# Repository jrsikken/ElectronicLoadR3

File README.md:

# Jasper's Electronic Load R3
This repositiry contains the open source hardware files. This device is an Arduino compatible Electronic Load. It is intended for testing DC power supplies, solar panels and batteries. It supports pulsed loads!
I am selling on Tindie https://www.tindie.com/products/jaspersikken/jaspers-electronic-load-r3/
Technical details are also found there.

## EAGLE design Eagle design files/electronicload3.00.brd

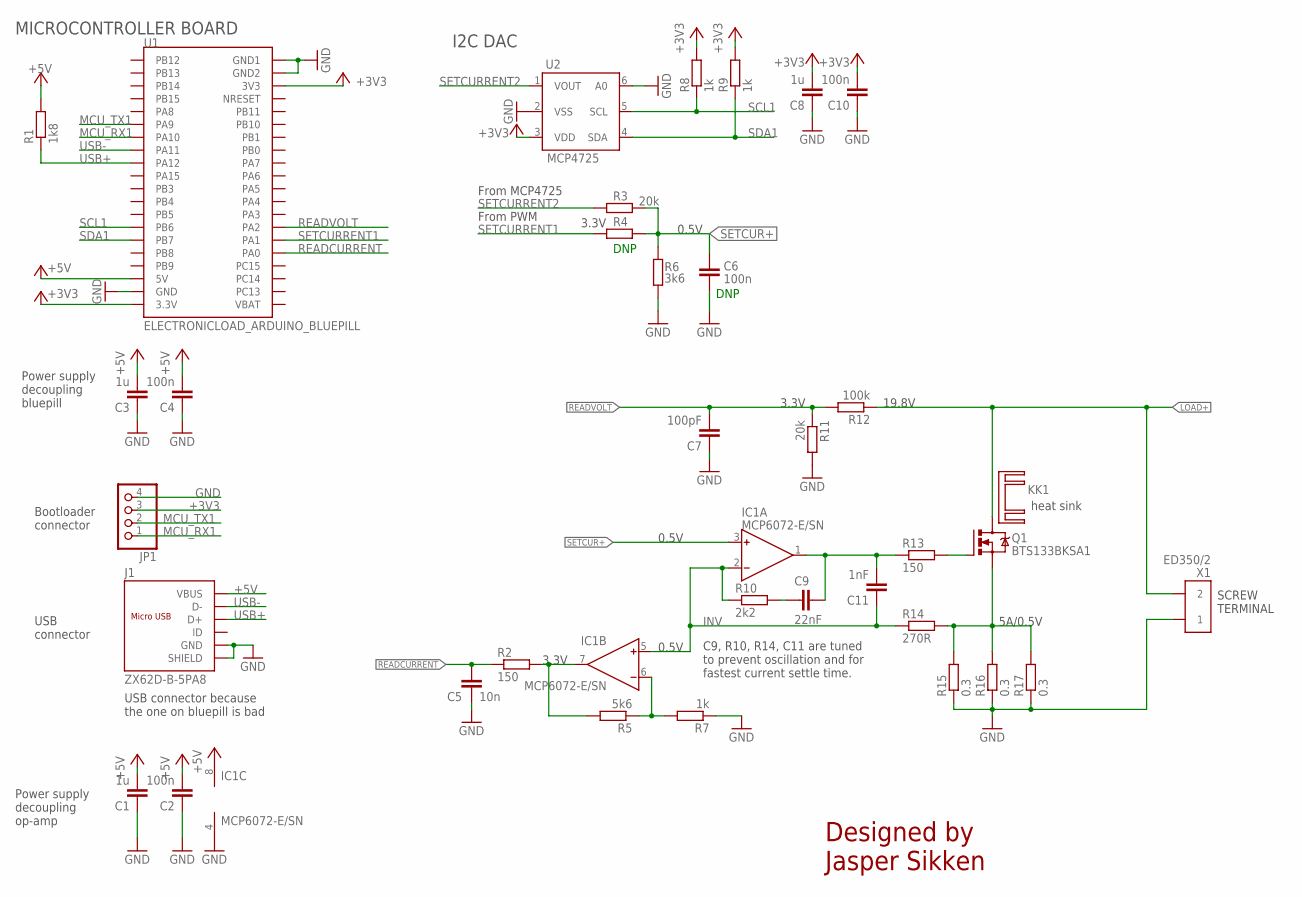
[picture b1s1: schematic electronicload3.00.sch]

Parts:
C1, C3, C8: 1u; C0603K; TOLERANCE 10%; VOLTAGE 16V; DIGIKEY 311-1444-1-ND
C2, C4, C10: 100n; C0603K; TOLERANCE 10%; VOLTAGE 50V; DIGIKEY 445-7456-1-ND
C5: 10n; C0603K; TOLERANCE 10%; VOLTAGE 50V; DIGIKEY 445-7456-1-ND
C6: 100n; C0603K; TOLERANCE 10%; VOLTAGE 50V; DIGIKEY 445-12511-1-ND
C7: 100pF; C0603K; TOLERANCE 10%; VOLTAGE 50V; DIGIKEY 445-7456-1-ND
C9: 22nF; C0603K; TOLERANCE 10%; VOLTAGE 50V; DIGIKEY 445-7456-1-ND
C11: 1nF; C0603K; TOLERANCE 10%; VOLTAGE 50V; DIGIKEY 445-7456-1-ND
IC1: MCP6072-E/SN; SO8
J1: ZX62D-B-5PA8; MICRO-USB5+6P-SMD-0.65-AB
JP1: PINHD-1X4; 1X04
KK1: SK129; SK129-HOLE
Q1: BTS133BKSA1; TO220BV; DIGIKEY BTS133BKSA1-ND
R1: 1k8; R0603; DIGIKEY RMCF0603JT18K0CT-ND
R2, R13: 150; R0603; DIGIKEY RMCF0603JT150RCT-ND
R3, R4: 20k; R0603; DIGIKEY RMCF0603JT18K0CT-ND
R5: 5k6; R0603; DIGIKEY RMCF0603JT180KCT-ND
R6: 3k6; R0603; DIGIKEY RMCF0603JT18K0CT-ND
R7: 1k; R0603; DIGIKEY RMCF0603JT20K0CT-ND
R8, R9: 1k; R0603; DIGIKEY RMCF0603JT10K0CT-ND
R10: 2k2; R0603; DIGIKEY RMCF0603JT150RCT-ND
R11: 20k; R0603; DIGIKEY RMCF0603JT20K0CT-ND
R12: 100k; R0603; DIGIKEY RMCF0603JT100KCT-ND
R14: 270R; R0603; DIGIKEY RMCF0603JT150RCT-ND
R15, R16, R17: 0.3; R2512
U1: ELECTRONICLOAD_ARDUINO_BLUEPILL
U2: MCP4725; SOT-23-6
X1: ED350/2

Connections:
+3V3: C8.2, C10.2, JP1.3, R8.2, R9.2, U1.P$17 (3V3), U1.P$39 (3.3V), U2.3 (VDD)
+5V: C1.2, C2.2, C3.2, C4.2, IC1.8 (V+), J1.1 (VBUS), R1.2, U1.P$37 (5V)
AOUT: C9.1, C11.2, IC1.1 (OUT), R13.1
GATE: Q1.G, R13.2
GND: C1.1, C2.1, C3.1, C4.1, C5.1, C6.1, C7.1, C8.1, C10.1, IC1.4 (V-), J1.5 (GND), J1.P1 (SHIELD), J1.P2 (SHIELD), J1.P3 (SHIELD), J1.P4 (SHIELD), J1.P5 (SHIELD), J1.P6 (SHIELD), JP1.4, R6.1, R7.1, R11.2, R15.1, R16.1, R17.1, U1.P$18 (GND2), U1.P$19 (GND1), U1.P$38 (GND), U2.2 (VSS), U2.6 (A0), X1.P$1 (1)
INV: C11.1, IC1.2 (IN-), IC1.5 (IN+), R10.1, R14.1
LOAD+: Q1.D, R12.1, X1.P$2 (2)
MCU_RX1: JP1.1, U1.P$26 (PA10)
MCU_TX1: JP1.2, U1.P$25 (PA9)
unnamed: Q1.S, R14.2, R15.2, R16.2, R17.2
unnamed: IC1.6 (IN-), R5.1, R7.2
unnamed: C9.2, R10.2
unnamed: IC1.7 (OUT), R2.2, R5.2
READCURRENT: C5.2, R2.1, U1.P$4 (PA0)
READVOLT: C7.2, R11.1, R12.2, U1.P$6 (PA2)
SCL1: R8.1, U1.P$33 (PB6), U2.5 (SCL)
SDA1: R9.1, U1.P$34 (PB7), U2.4 (SDA)
SETCUR+: C6.2, IC1.3 (IN+), R3.1, R4.1, R6.2
SETCURRENT1: R4.2, U1.P$5 (PA1)
SETCURRENT2: R3.2, U2.1 (VOUT)
USB+: J1.3 (D+), R1.1, U1.P$28 (PA12)
USB-: J1.2 (D-), U1.P$27 (PA11)

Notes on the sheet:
SCREW TERMINAL
19.8V
3.3V
MICROCONTROLLER BOARD
I2C DAC
Bootloader connector
From MCP4725
From PWM
DNP
Designed by Jasper Sikken
USB connector because the one on bluepill is bad
USB connector
Power supply decoupling bluepill
Power supply decoupling op-amp
heat sink
C9, R10, R14, C11 are tuned to prevent oscillation and for fastest current settle time.
5A/0.5V
0.5V

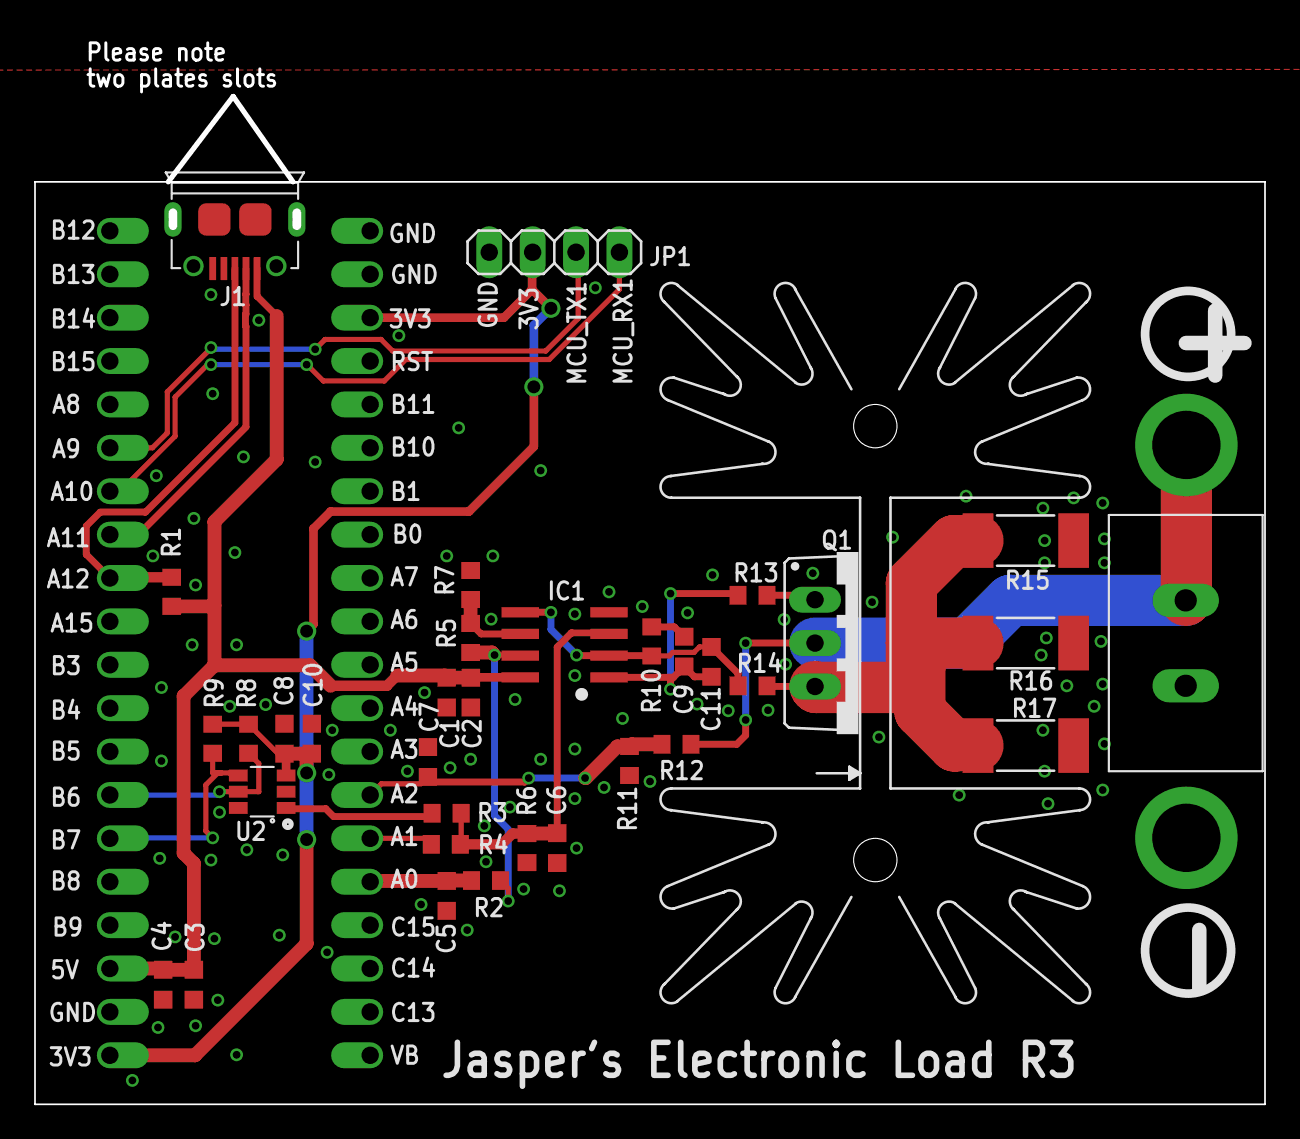
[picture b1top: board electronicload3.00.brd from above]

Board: 2 copper layers, 72.0 x 59.0 mm, 36 parts (0 on the bottom side), 22 nets.

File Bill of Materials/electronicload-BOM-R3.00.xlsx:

Qty | Value | Device | Package | Parts | Description | DIGIKEY | FARNELL_OC | MF | MOUSER_OC | MPN | SPICEPREFIX | TEMPCOEFF | TOLERANCE | VALUE.1 | VOLTAGE | Column1
3 | 0.3 | R2512_10R | R2512 | R15, R16, R17 | Resistor |  | 2426553
1 | 100k | R-EU_R0603 | R0603 | R12 | Resistor |  |  |  |  |  | R
3 | 100n | C-EUC0603K | C0603K | C2, C4, C10 | Capacitor |  |  |  |  |  | C | X5R | 0.1 |  | 50V
1 | 1nF | C-EUC0603K | C0603K | C11 | Capacitor
1 | 10nF | C-EUC0603K | C0603K | C5 | Capacitor
1 | 22nF | C-EUC0603K | C0603K | C9 | Capacitor
1 | 100pF | C-EUC0603K | C0603K | C7 | Capacitor
2 | 150R | R-EU_R0603 | R0603 | R2, R13 | Resistor |  |  |  |  |  | R
1 | 270R | R-EU_R0603 | R0603 | R14 | Resistor
3 | 1k | R-EU_R0603 | R0603 | R7, R8, R9 | Resistor |  |  |  |  |  | R
1 | 1k8 | R-EU_R0603 | R0603 | R1 | Resistor |  |  |  |  |  | R
1 | 2k2 | R-EU_R0603 | R0603 | R10 | Resistor
5 | 1u | C-EUC0603K | C0603K | C1, C3, C8 | Capacitor |  |  |  |  |  | C | X5R | 0.1 |  | 16V
2 | 20k | R-EU_R0603 | R0603 | R3, R11 | resistor |  |  |  |  |  | R
1 | 3k6 | R-EU_R0603 | R0603 | R6 | resistor |  |  |  |  |  | R
1 | 5k6 | R-EU_R0603 | R0603 | R5 | Resistor |  |  |  |  |  | R
1 | BTS133BKSA1 | BTS133BKSA1 | TO220BV | Q1 | mosfet | BTS133BKSA1-ND | 2480556 |  | 726-BTS133BKSA1
1 | ED350/2 | KF128-2P | KF128-2P | X1 | KF128-2P (5.08 mm) TERMINAL BLOCK
1 | ARDUINO_BLUEPILL | ARDUINO_BLUEPILL | ARDUINO_BLUEPILL | U1 | footprint for bluepill (STM32F103)
1 | MCP4725 | MCP4725 | SOT-23-6 | U2 | 12-Bit Digital-to-Analog Converter with EEPROM Memory | MCP4725A1T-E/CHCT-ND
1 | MCP6072-E/SN | MCP6072-E/SN | SO8 | IC1 | Dual opamp
1 | AK-122 | SK129-HOLE |  | KK1 | Aluminum Heatsink Ak-122 H=45mm 42x25x45mm Color=Natural TO-TO-220
1 | 530002B02500G | SK129-HOLE |  | KK1-alternative | Aluminum Heatsink H=63.5mm 42x25x63mm Black TO-TO-220 |  | AAVID THERMALLOY | 530002B02500G
1 | ZX62D-B-5PA8 | MICRO-USB-SMD | MICRO-USB5+6P-SMD-0.65-AB | J1 | Micro USB connector |  | 2554981 | Hirose |  | ZX62D-B-5PA8 |  |  |  | ZX62D-B-5PA8

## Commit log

2018-09-01 FIrst release
2018-09-01 Corrected BOM and eagle files before devices are manufactured
2018-09-15 Update LICENSE
2018-09-26 added schematic in in png format
